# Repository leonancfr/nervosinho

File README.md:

# Projeto Macunaíma

Repositório para controle de versão de:
- Placa do Sistema Nervoso Segunda Geração, a.k.a Nervosinho
- Placa da expansão para bateria(BMS)
- Script de testes de fábrica do hardware
- Desenho da case e da caixa de transporte
- Projeto Elétrico da caixa técnica para Gabriel Cidades

## Change log das versões de hardware:
[Página do notion com o change log](https://www.notion.so/gabrieltecnologia/Change-log-das-vers-es-de-Hardware-a60b3e2a824349809387a2612b9022dc?pvs=4)

## Repositórios relacionados
- [Firmware do STM32 presente no nervosinho](https://gitlab.com/gabriel-technologia/hardware#:~:text=Firmware%20Supervisor%20Nervosinho)
- [CharlinhOS - Sistema Operacional do Processador do Nervosinho](https://gitlab.com/gabriel-technologia/iot/charlinhos)
- [CharlesGO - Software que conecta o dispositivo à infraestrutura da Gabriel](https://gitlab.com/gabriel-technologia/iot/charlesgo)

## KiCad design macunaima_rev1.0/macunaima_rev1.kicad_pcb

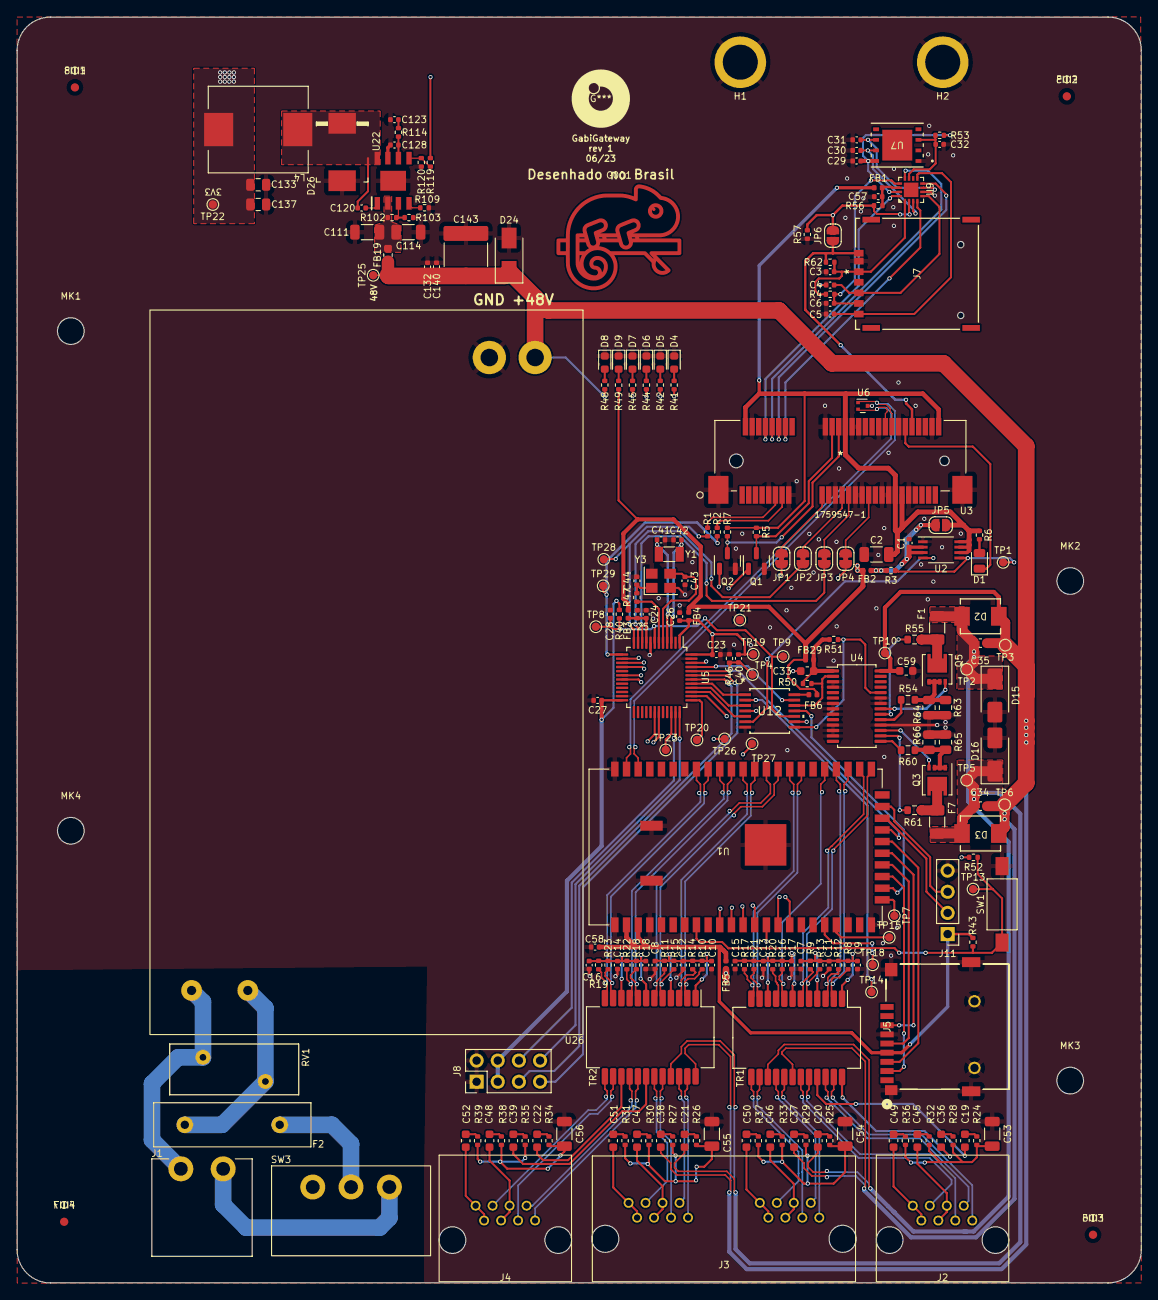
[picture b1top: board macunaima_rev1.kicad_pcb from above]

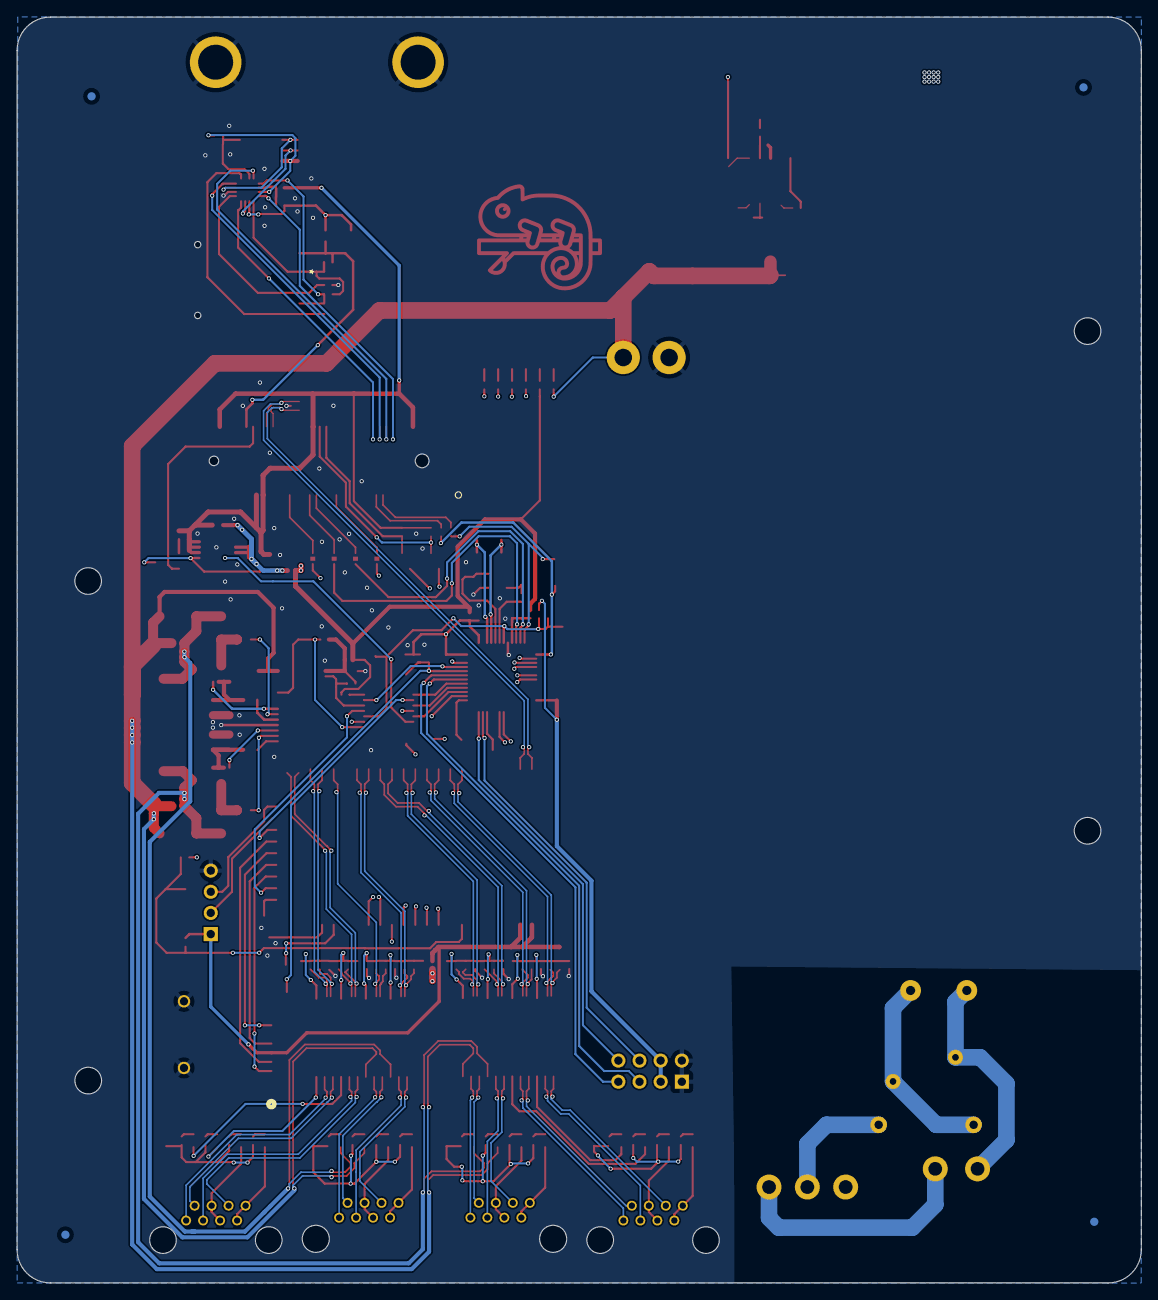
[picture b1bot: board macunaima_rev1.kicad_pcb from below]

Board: 4 copper layers, 135.0 x 152.0 mm, 239 parts (4 on the bottom side), 184 nets.

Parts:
C1: 1uF/6.3V; C_0402_1005Metric
C2: 150uF/6.3V; C_1206_3216Metric
C3, C29, C57: 100nF/6.3V; C_0402_1005Metric
C4, C5, C6, C30, C31, C32: 33pF/6.3V; C_0402_1005Metric
C7, C8, C9, C10, C11, C12, C13, C14, C15, C16, C17, C18: 0.1uF; C_0402_1005Metric
C19, C20, C21, C22, C36, C37, C38, C39, C45, C46, C47, C48, C49, C50, C51, C52: 22nF/100V; C_0603_1608Metric
C23, C26, C28, C40, C58: 100nF; C_0402_1005Metric
C24: 10nF; C_0402_1005Metric
C25: 1uF; C_0402_1005Metric
C27: 4.7uF; C_0402_1005Metric
C33: 100nF/50V; C_0603_1608Metric
C34, C35, C59: 100nF/100V; C_0603_1608Metric
C41, C42: 10pF; C_0402_1005Metric
C43, C44: 20pF; C_0402_1005Metric
C53, C54, C55, C56: 1000pF/2kV; C_1206_3216Metric
C111, C114: 2.2uF/100V; C_1206_3216Metric
C120, C132, C140: 100nF/100V; C_0402_1005Metric
C123: 6.8nF/50V; C_0402_1005Metric
C128: 39pF/50V; C_0402_1005Metric
C133, C137: 47uF/10V; C_0805_2012Metric
C143: 10uF/100V; C_2220_5650Metric
D1: LED; LED_0805_2012Metric
D2, D3: SMBJ58A; CR_SM12CA-13-F_DIO
D4, D5, D6, D7, D8, D9: LED_Small; LED_0603_1608Metric
D15, D16: 10MQ100NTRPBF; D_SMA
D24: SMAJ51A; D_SMA
D26: B560C; DO-214AB
F1, F7: 046801.5NR; Fuse_1206_3216Metric
F2: LVR100S-240; Fuse_Littelfuse-LVR100
FB1, FB2, FB3, FB4, FB5, FB6, FB29: FerriteBead_Small; L_0402_1005Metric
FB19: FerriteBead_Small; L_0603_1608Metric
FID1, FID2, FID3, FID4, FID5, FID6, FID7, FID8: Fiducial; Fiducial_1mm_Mask2mm
G001: LOGO; camaleaosilk
H1, H2: MountingHole_Pad; 4882 Standoff
J1: 127VAC/220VAC; WJ2EDGRC-5.08-2P
J2, J4: 8P8C; HC-RJ45-5JA-1-6
J3: RJ45_x2; HC-RJ45-5JA-2-6
J5: Micro_SD_Card_Det1; CONN9_0185-02_GSW
J7: XKNANO-113; XKNANO-113_XKB
J8: Conn_02x04_Odd_Even; PinHeader_2x04_P2.54mm_Vertical
J11: Conn_01x04; PinHeader_1x04_P2.54mm_Vertical
JP1, JP2, JP3, JP4: SolderJumper_2_Bridged; SolderJumper-2_P1.3mm_Bridged_RoundedPad1.0x1.5mm
JP5, JP6: SolderJumper_2_Open; SolderJumper-2_P1.3mm_Open_RoundedPad1.0x1.5mm
L4: 8.2uH; MHCC10040-8R2M-R7
MK1, MK2, MK3, MK4: Mounting_Hole; MountingHole_3.2mm_M3
Q1, Q2: PDTC143ZT; SOT-23
Q3, Q5: CSD19538Q3A; Diodes_PowerDI3333-8
R1, R2: 330R; R_0402_1005Metric
R3, R40, R43, R46, R50, R51, R52, R56, R62: 10k; R_0402_1005Metric
R4, R53: 15k; R_0402_1005Metric
R5, R7: 5k1; R_0402_1005Metric
R6: 220R; R_0402_1005Metric
R8, R9, R10, R11, R12, R13, R14, R15, R16, R17, R18, R19, R20, R21, R22, R23: 50R; R_0402_1005Metric
R24, R25, R26, R27, R28, R29, R30, R31, R32, R33, R34, R35, R36, R37, R38, R39: 75R; R_0402_1005Metric
R41, R42, R44, R45, R48, R49: R_Small; R_0402_1005Metric
R47: 390R; R_0402_1005Metric
R54, R60: 22.1R; R_0603_1608Metric
R55, R61: 47R; R_0603_1608Metric
R57: NOPOP; R_0402_1005Metric
R63, R64, R65, R66: 0.510R; R_0805_2012Metric
R102: 523k; R_0402_1005Metric
R103: 84k5; R_0402_1005Metric
R109: 162k; R_0402_1005Metric
R114: 13k; R_0402_1005Metric
R119: 36k5; R_0402_1005Metric
R120: 11k8; R_0402_1005Metric
RV1: 391KD14J; RV_Disc_D15.5mm_W6.1mm_P7.5mm
SW1: BOOT; SW_SPST_FSMSM
SW3: SW_SPDT; L102011MS02Q
TP1, TP2, TP3, TP4, TP5, TP6, TP7, TP8, TP9, TP10, TP13, TP14, TP15, TP18, TP19, TP20, TP21, TP22, TP23, TP25, TP26, TP27, TP28, TP29: TestPoint; TestPoint_Pad_D1.0mm
TR1, TR2: 30F-51NL; Transformer_Ethernet_YDS_30F-51NL_SO-24_7.1x15.1mm
U1: HLK-7628
U2: BD82006FVJ-M; BD82006FVJ-MGE2
U3: 1759547-1
U4: TPS23861; TSSOP-28_4.4x9.7mm_P0.65mm
U5: STM32F030C8Tx; LQFP-48_7x7mm_P0.5mm
U6: TPD2EUSB30; SOT-723
U7: NOPOP; SIM-ST-MFF2_HOL-M
U9: FSA2567MPX; MLP16
U12: 74HC04PW_118; TSSOP14_74HC04_NEX
U22: TPS54360BDDAR; SOIC127P600X170-9N
U26: IRM-60-48; IRM-60
Y1: 32.768kHz; Crystal_SMD_3215-2Pin_3.2x1.5mm
Y3: 8MHz; Crystal_SMD_3225-4Pin_3.2x2.5mm

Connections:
/EPHY_LED0: R41.1, U1.13 (EPHY_LED0)
/EPHY_LED1: R42.1, U1.12 (EPHY_LED1)
/EPHY_LED2: R44.1, U1.11 (EPHY_LED2)
/EPHY_LED3: R45.1, U1.10 (EPHY_LED3)
/ETH1_POE+: C34.1, C35.2, C37.1, C38.1, C59.2, C132.1, C140.1, C143.1, D2.1 (A1), D3.1 (A1), D24.1, FB19.1, R48.1, TP3.1, TP6.1, TP10.1, TP25.1, TR1.18 (CT), TR2.24 (CT), U4.28 (VPWR), U26.4 (+Vout)
/ETH1_POE-: C20.1, C35.1, D2.2 (A2), D15.1 (K), F1.2, TP2.1, TR1.15 (CT)
/ETH2_POE-: C21.1, C34.2, D3.2 (A2), D16.1 (K), F7.2, TP5.1, TR2.21 (CT)
/Ethernet connectors/TR1P1+: J2.1, TR1.23 (MX1+)
/Ethernet connectors/TR1P1-: J2.2, TR1.22 (MX1-)
/Ethernet connectors/TR1P2+: J2.3, TR1.20 (MX2+)
/Ethernet connectors/TR1P2-: J2.6, TR1.19 (MX2-)
/Ethernet connectors/TR1P3+: J3.1, TR1.17 (MX3+)
/Ethernet connectors/TR1P3-: J3.2, TR1.16 (MX3-)
/Ethernet connectors/TR1P4+: J3.3, TR1.14 (MX4+)
/Ethernet connectors/TR1P4-: J3.6, TR1.13 (MX4-)
/Ethernet connectors/TR2P1+: J3.9, TR2.23 (MX1+)
/Ethernet connectors/TR2P1-: J3.10, TR2.22 (MX1-)
/Ethernet connectors/TR2P2+: J3.11, TR2.20 (MX2+)
/Ethernet connectors/TR2P2-: J3.14, TR2.19 (MX2-)
/Ethernet connectors/TR2P3+: J4.1, TR2.17 (MX3+)
/Ethernet connectors/TR2P3-: J4.2, TR2.16 (MX3-)
/Ethernet connectors/TR2P4+: J4.3, TR2.14 (MX4+)
/Ethernet connectors/TR2P4-: J4.6, TR2.13 (MX4-)
/HLK7628_RX: TP26.1, U1.16 (UART_RXD1), U5.30 (PA9)
/HLK7628_TX: TP27.1, U1.15 (UART_TXD1), U5.31 (PA10)
/HLK-7628 Module/GPIO2: TP18.1, U1.19 (I2S_WS)
/HLK-7628 Module/GPIO3: TP15.1, U1.20 (I2S_CLK)
/HLK-7628 Module/GPIO4: TP7.1, U1.24 (I2C_SCLK)
/HLK-7628 Module/HLK7628_3V3: C58.1, FB5.2, J5.4 (VDD), J11.1, R43.2, U1.2 (3.3VD), U1.3 (3.3VD)
/HLK-7628 Module/MISO: J5.7 (DAT0), U1.28 (SPI_MISO)
/HLK-7628 Module/MOSI: J5.3 (CMD), U1.29 (SPI_MOSI)
/HLK-7628 Module/SCK: J5.5 (CLK), U1.27 (SPI_CLK)
/HLK-7628 Module/SD_CS: J5.2 (DAT3/CD), U1.26 (SPI_CS1)
/HLK-7628 Module/UART_RXD0: J11.3, U1.32 (UART_RXD0)
/HLK-7628 Module/UART_TXD0: J11.2, U1.31 (UART_TXD0)
/MDI_P0_R_N: R9.1, TR1.6 (TD2-), U1.35 (MDI_RN_P0)
/MDI_P0_R_P: R13.1, TR1.5 (TD2+), U1.34 (MDI_RP_P0)
/MDI_P0_T_N: R12.2, TR1.3 (TD1-), U1.37 (MDI_TN_P0)
/MDI_P0_T_P: R8.2, TR1.2 (TD1+), U1.36 (MDI_TP_P0)
/MDI_P1_R_N: R17.1, TR1.12 (TD4-), U1.41 (MDI_RN_P1)
/MDI_P1_R_P: R21.1, TR1.11 (TD4+), U1.40 (MDI_RP_P1)
/MDI_P1_T_N: R20.2, TR1.9 (TD3-)
/MDI_P1_T_P: R16.2, TR1.8 (TD3+), U1.38 (MDI_TP_P1)
/MDI_P2_R_N: R11.1, TR2.6 (TD2-), U1.43 (MDI_RN_P2)
/MDI_P2_R_P: R15.1, TR2.5 (TD2+), U1.42 (MDI_RP_P2)
/MDI_P2_T_N: R14.2, TR2.3 (TD1-), U1.45 (MDI_TN_P2)
/MDI_P2_T_P: R10.2, TR2.2 (TD1+), U1.44 (MDI_TP_P2)
/MDI_P3_R_N: R19.1, TR2.12 (TD4-), U1.49 (MDI_RN_P3)
/MDI_P3_R_P: R23.1, TR2.11 (TD4+), U1.48 (MDI_RP_P3)
/MDI_P3_T_N: R22.2, TR2.9 (TD3-), U1.47 (MDI_TN_P3)
/MDI_P3_T_P: R18.2, TR2.8 (TD3+), U1.46 (MDI_TP_P3)
/MODEM_CTS: JP2.1 (A), U5.11 (PA1)
/MODEM_DTR: JP4.1 (A), U5.19 (PB1)
/MODEM_EN: U2.4 (EN), U12.6 (3Y)
/MODEM_RING: JP1.1 (A), U5.18 (PB0)
/MODEM_RTS: JP3.1 (A), U5.10 (PA0)
/MODEM_RX: R1.1, TP28.1, U5.12 (PA2)
/MODEM_TX: R2.1, TP29.1, U5.13 (PA3)
/MODEM_USB_D_N: U1.55 (USB_DM), U3.36, U6.2 (D-)
/MODEM_USB_D_P: U1.54 (USB_DP), U3.38, U6.1 (D+)
/Mini PCIe/2FF_CLK: C5.1, J7.C3 (CLK), U9.9 (1CLK)
/Mini PCIe/2FF_DATA: C6.1, J7.C7 (I/O), R4.2, U9.13 (1DATA)
/Mini PCIe/2FF_RST: C4.1, J7.C2 (RST), U9.5 (1RST)
/Mini PCIe/2FF_VCC: C3.1, J7.C1 (VCC), R4.1, R62.2, U9.1 (1VSIM)
/Mini PCIe/LED_WWAN: D1.1 (K), U3.42
/Mini PCIe/MFF2_CLK: C31.1, U7.6 (CLK), U9.7 (2CLK)
/Mini PCIe/MFF2_DATA: C32.1, R53.2, U7.3 (I/O), U9.11 (2DATA)
/Mini PCIe/MFF2_RST: C30.1, U7.7 (RST), U9.3 (2RST)
/Mini PCIe/MFF2_VCC: C29.1, R53.1, U7.8 (VCC), U9.15 (2VSIM)
/Mini PCIe/MODEM_3V3: C2.1, FB1.1, JP5.2 (B), R5.1, R6.1, R7.1, U2.6 (OUT), U2.7 (OUT), U2.8 (OUT), U3.2, U3.24, U3.39, U3.41, U3.52
/Mini PCIe/MODEM_FAULT: R3.1, TP1.1, U2.5 (/OC)
/Mini PCIe/PERST: Q2.3 (C), R7.2, U3.22
/Mini PCIe/SIM_CLK: U3.12, U9.8 (CLK)
/Mini PCIe/SIM_DATA: U3.10, U9.12 (DATA)
/Mini PCIe/SIM_RST: U3.14, U9.4 (RST)
/Mini PCIe/SIM_VDD: U3.8, U9.16 (VSIM)
/Mini PCIe/SWITCH_VCC: C57.1, FB1.2, R56.2, U9.14 (VCC)
/Mini PCIe/W_DISABLE: Q1.3 (C), R5.2, U3.20
/P0RST_N: TP14.1, U1.14 (P0RST_N), U12.2 (1Y)
/PERST_CTL: Q2.1 (B), U5.15 (PA5)
/PMS_3V3: C133.2, C137.2, FB2.1, FB3.1, FB4.2, FB5.1, FB6.2, FB29.1, L4.2, R49.1, R119.1, TP22.1
/Power Management/Fase: J1.2, SW3.3 (C)
/Power Management/Neutro: J1.1, RV1.1, U26.1 (AC/N)
/Power over Ethernet/TPS23861_VDD: C33.2, FB29.2, R50.2, R51.2, U4.1 (VDD)
/RESET_POE: R50.1, U4.2 (~RESET), U12.12 (6Y)
/SHUTDOWN_POE: R51.1, U4.24 (~SHTDWN), U12.8 (4Y)
/SIMCARD_DETECT: J7.CD, JP6.1 (A), R62.1, U3.44, U5.46 (PB9)
/SIMCARD_SEL: JP6.2 (B), R56.1, R57.2, U5.14 (PA4), U9.2 (SEL)
/STM32 circuit/NRST: C28.1, R40.2, TP8.1, TP9.1, U5.7 (NRST), U12.10 (5Y)
/STM32 circuit/OSC32_IN: C42.1, U5.3 (PC14), Y1.2
/STM32 circuit/OSC32_OUT: C41.1, U5.4 (PC15), Y1.1
/STM32 circuit/OSC_IN: C43.1, U5.5 (PF0), Y3.3
/STM32 circuit/OSC_OUT: R47.1, U5.6 (PF1)
/STM32 circuit/STM32_I2C1_SCL: J8.5, U5.42 (PB6)
/STM32 circuit/STM32_I2C1_SDA: J8.7, U5.43 (PB7)
/STM32 circuit/STM32_I2C2_SCL: J8.6, U5.35 (PF6)
/STM32 circuit/STM32_I2C2_SDA: J8.8, U5.36 (PF7)
/STM32 circuit/STM32_PA15: U5.38 (PA15), U12.9 (4A)
/STM32 circuit/STM32_PB3: U5.39 (PB3), U12.5 (3A)
/STM32 circuit/STM32_PB4: U5.40 (PB4), U12.3 (2A)
/STM32 circuit/STM32_PB5: U5.41 (PB5), U12.1 (1A)
/STM32 circuit/STM32_PB8: U5.45 (PB8), U12.13 (6A)
/STM32 circuit/STM32_VDD: C23.1, C26.1, C27.1, C40.1, FB4.1, J8.3, J8.4, R40.1, TP19.1, U5.1 (VDD), U5.24 (VDD), U5.48 (VDD)
/STM32 circuit/STM32_VDDA: C24.2, C25.1, FB3.2, U5.9 (VDDA)
/STM32 circuit/SWCLK: TP20.1, U5.37 (PA14)
/STM32 circuit/SWDIO: TP23.1, U5.34 (PA13)
/STM32 circuit/~STM32_PB4: R52.2, U12.4 (2Y)
/STM32_BOOT0: C40.2, R46.1, TP4.1, U1.30 (GPIO0), U5.44 (BOOT0)
/STM32_RST: U1.25 (I2C_SD), U12.11 (5A)
/WDT_RST_N: R43.1, R52.1, SW1.1 (A), TP13.1, U1.8 (WDT_RST_N)
/W_DISABLE_CTL: Q1.1 (B), U5.16 (PA6)
GND: C1.1, C2.2, C3.2, C4.2, C5.2, C6.2, C7.2, C8.2, C9.2, C10.2, C11.1, C12.1, C13.2, C14.2, C15.2, C16.2, C17.1, C18.1, C23.2, C24.1, C25.2, C26.2, C27.2, C28.2, C29.2, C30.2, C31.2, C32.2, C33.1, C41.2, C42.2, C43.2, C44.2, C53.1, C54.1, C55.1, C56.1, C57.2, C58.2, C59.1, C111.1, C114.2, C123.1, C128.1, C132.2, C133.1, C137.1, C140.2, C143.2, D4.1 (K), D5.1 (K), D6.1 (K), D7.1 (K), D8.1 (K), D9.1 (K), D15.2 (A), D16.2 (A), D24.2, D26.A, H1.1, H2.1, J5.6 (VSS), J5.10 (SHIELD), J5.11 (SHIELD), J5.12 (SHIELD), J5.13 (SHIELD), J5.14 (SHIELD), J5.15 (SHIELD), J7.C5 (GND), J8.1, J8.2, J11.4, Q1.2 (E), Q2.2 (E), R46.2, R57.1, R63.2, R64.2, R65.1, R66.1, R103.2, R109.2, R120.2, SW1.2 (B), TP21.1, U1.1 (GND), U1.4 (GND), U1.21 (GND), U1.23 (GND), U1.56 (GND), U1.57 (GND), U1.58 (GND), U1.59 (GND), U2.1 (GND), U3.4, U3.9, U3.15, U3.18, U3.21, U3.26, U3.27, U3.28, U3.29, U3.34, U3.35, U3.37, U3.40, U3.43, U3.50, U3.53, U3.54, U4.3 (SCL), U4.4 (SDAI), U4.7 (DGND), U4.8 (SEN3), U4.9 (DRAIN3), U4.11 (KSENSB), U4.12 (SEN4), U4.13 (DRAIN4), U4.18 (KSENSA), U4.22 (AGND), U4.23 (A3), U5.8 (VSSA), U5.23 (VSS), U5.47 (VSS), U6.3 (GND), U7.1 (GND), U9.6 (GND), U12.7 (GND), U22.7 (GND), U22.9 (PAD), U26.3 (-Vout), Y3.2, Y3.4
unnamed: C8.1, C10.1, C12.2, R10.1, R11.2, R14.1, R15.2, TR2.1 (CT), TR2.4 (CT)
unnamed: C7.1, C9.1, C11.2, R8.1, R9.2, R12.1, R13.2, TR1.1 (CT), TR1.4 (CT)
unnamed: C13.1, C15.1, C17.2, R16.1, R17.2, R20.1, R21.2, TR1.7 (CT), TR1.10 (CT)
unnamed: C14.1, C16.1, C18.2, R18.1, R19.2, R22.1, R23.2, TR2.7 (CT), TR2.10 (CT)
unnamed: C19.1, TR1.21 (CT)
unnamed: C19.2, R24.1
unnamed: C20.2, R25.1
unnamed: C21.2, R26.1
unnamed: C22.1, TR2.15 (CT)
unnamed: C22.2, R34.1
unnamed: C36.1, TR1.24 (CT)
unnamed: C36.2, R28.1
unnamed: C37.2, R29.1
unnamed: C38.2, R27.1
unnamed: C39.1, TR2.18 (CT)
unnamed: C39.2, R35.1
unnamed: C44.1, R47.2, Y3.1
unnamed: C45.1, J2.4, J2.5
unnamed: C45.2, R32.1
unnamed: C46.1, J3.4, J3.5
unnamed: C46.2, R33.1
unnamed: C47.1, J3.12, J3.13
unnamed: C47.2, R30.1
unnamed: C48.1, J4.4, J4.5
unnamed: C48.2, R38.1
unnamed: C49.1, J2.7, J2.8
unnamed: C49.2, R36.1
unnamed: C50.1, J3.7, J3.8
unnamed: C50.2, R37.1
unnamed: C51.1, J3.15, J3.16
unnamed: C51.2, R31.1
unnamed: C52.1, J4.7, J4.8
unnamed: C52.2, R39.1
unnamed: C53.2, R24.2, R28.2, R32.2, R36.2
unnamed: C54.2, R25.2, R29.2, R33.2, R37.2
unnamed: C55.2, R26.2, R27.2, R30.2, R31.2
unnamed: C56.2, R34.2, R35.2, R38.2, R39.2
unnamed: C123.2, R114.2
unnamed: D1.2 (A), R6.2
unnamed: D4.2 (A), R41.2
unnamed: D5.2 (A), R42.2
unnamed: D6.2 (A), R44.2
unnamed: D7.2 (A), R45.2
unnamed: D8.2 (A), R48.2
unnamed: D9.2 (A), R49.2
unnamed: F1.1, Q5.5 (D), R55.2
unnamed: F7.1, Q3.5 (D), R61.2
unnamed: JP1.2 (B), U3.17
unnamed: JP2.2 (B), U3.23
unnamed: JP3.2 (B), U3.25
unnamed: JP4.2 (B), U3.31
unnamed: C1.2, FB2.2, JP5.1 (A), R3.2, U2.2 (IN), U2.3 (IN)
unnamed: Q3.4 (G), U4.17 (GATE1)
unnamed: Q3.1 (S), Q3.2 (S), Q3.3 (S), R60.2, R65.2, R66.2
unnamed: Q5.4 (G), U4.21 (GATE2)
unnamed: Q5.1 (S), Q5.2 (S), Q5.3 (S), R54.2, R63.1, R64.1
unnamed: R1.2, U3.11
unnamed: R2.2, U3.13
unnamed: F2.1, SW3.2 (B)
unnamed: R61.1, U4.16 (DRAIN1)
unnamed: R55.1, U4.20 (DRAIN2)
unnamed: R60.1, U4.15 (SEN1)
unnamed: R54.1, U4.19 (SEN2)
unnamed: FB6.1, U12.14 (VCC)
unnamed: C120.1, U22.1 (BOOT)
unnamed: C128.2, R114.1, U22.6 (COMP)
unnamed: R102.2, R103.1, U22.3 (EN)
unnamed: R119.2, R120.1, U22.5 (FB)
unnamed: R109.1, U22.4 (RT/CLK)
unnamed: C120.2, D26.K, L4.1, U22.8 (SW)
unnamed: C111.2, C114.1, FB19.2, R102.1, U22.2 (VIN)
unnamed: F2.2, RV1.2, U26.2 (AC/L)

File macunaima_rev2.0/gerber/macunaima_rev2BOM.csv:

Id,Designator,Footprint,Quantity,Comment,LCSC Part Number
11,C1,C_0402_1005Metric,1,1uF/6.3V,C307427
18,"C111,C114",C_1206_3216Metric,2,2.2uF/100V,C170101
9,"C120,C140,C132",C_0402_1005Metric,3,100nF/100V,C162178
57,C123,C_0402_1005Metric,1,6.8nF/50V,C2760541
48,C128,C_0402_1005Metric,1,39pF/50V,C1563
62,"C137,C133",C_0805_2012Metric,2,47uF/10V,C76636
88,C143,C_2220_5650Metric,1,10uF/100V,C153035
75,C2,C_1206_3216Metric,1,150uF/6.3V,C528968
22,"C23,C60,C28,C26,C58,C40",C_0402_1005Metric,6,100nF,C162178
61,C24,C_0402_1005Metric,1,10nF,C527014
6,C25,C_0402_1005Metric,1,1uF,C14445
40,C27,C_0402_1005Metric,1,4.7uF,C368809
80,"C3,C57,C29",C_0402_1005Metric,3,100nF/6.3V,C1525
4,"C32,C5,C30,C4,C6,C31",C_0402_1005Metric,6,33pF/6.3V,C1562
79,C33,C_0603_1608Metric,1,100nF/50V,C42998
41,"C34,C35,C59",C_0603_1608Metric,3,100nF/100V,C15725
2,"C38,C36,C46,C49,C45,C52,C48,C50,C37,C51,C21,C47,C19,C39,C20,C22",C_0603_1608Metric,16,22nF/100V,C313105
8,"C41,C42",C_0402_1005Metric,2,10pF,C513681
44,"C43,C44",C_0402_1005Metric,2,20pF,C1554
50,"C53,C54,C56,C55",C_1206_3216Metric,4,1000pF/2kV,C9196
19,"C9,C11,C18,C15,C12,C16,C17,C10,C7,C14,C8,C13",C_0402_1005Metric,12,0.1uF,C162178
15,D1,LED_0805_2012Metric,1,LED,C434432
59,"D16,D15",D_SMA,2,10MQ100NTRPBF,C241877
28,D24,D_SMA,1,SMAJ51A,C309894
54,D26,DO-214AB,1,B560C,C85100
34,"D3,D2",CR_SM12CA-13-F_DIO,2,SMBJ58A,C707476
47,"D7,D8,D4,D5,D6,D9",LED_0805_2012Metric,6,LED_Small,C434432
52,"F1,F7",Fuse_1206_3216Metric,2,046801.5NR,C151143
17,F2,Fuse_Littelfuse-LVR100,1,LVR100S-240,C20876
31,FB19,L_0603_1608Metric,1,FerriteBead_Small,C394410
27,"FB6,FB29,FB2,FB1,FB4,FB5,FB3",L_0402_1005Metric,7,FerriteBead_Small,C275476
35,"FID3,FID1,FID2,FID4,FID6,FID8,FID7,FID5",Fiducial_1mm_Mask2mm,8,Fiducial,NOPOP
82,"H1,H2",SMTSO2545CTJ,2,MountingHole_Pad,C2916325
66,J1,WJ2EDGRC-5.08-2P,1,127VAC/220VAC,C3697
33,J11,PinHeader_1x04_P2.54mm_Vertical,1,Conn_01x04,NOPOP
36,J2,HC-RJ45-5JA-1-6,1,8P8C,C3000176
72,J3,HC-RJ45-5JA-2-4,1,RJ45_x2,C3000179
97,J4,HC-RJ45-5JA-1-6-L,1,8P8C,C3000188
51,J5,CONN9_0185-02_GSW,1,Micro_SD_Card_Det1,C5155564
56,J6,KF235-5.0-2P,1,Conn_01x02,C475172
77,J7,XKNANO-113_XKB,1,XKNANO-113,C381071
10,J8,PinHeader_2x04_P2.54mm_Vertical,1,Conn_02x04_Odd_Even,NOPOP
58,J9,KH-IPEX-SMAKWE-B120H,1,Conn_01x01,C530651
12,"JP1,JP3,JP4,JP2",SolderJumper-2_P1.3mm_Bridged_RoundedPad1.0x1.5mm,4,SolderJumper_2_Bridged,NOPOP
63,"JP6,JP5,JP8,JP9,JP7",SolderJumper-2_P1.3mm_Open_RoundedPad1.0x1.5mm,5,SolderJumper_2_Open,NOPOP
68,L4,MHCC10040-8R2M-R7,1,8.2uH,C285788
30,"MK2,MK1,MK3,MK4",MountingHole_4.3mm_M4,4,Mounting_Hole,NOPOP
70,"Q2,Q1",SOT-23,2,PDTC143ZT,C426852
46,"Q5,Q3",Diodes_PowerDI3333-8,2,CSD19538Q3A,C478471
49,"R1,R2",R_0402_1005Metric,2,330R,C105875
81,R102,R_0402_1005Metric,1,523k,C27011
94,R103,R_0402_1005Metric,1,84k5,C185390
67,R109,R_0402_1005Metric,1,162k,C321325
85,R114,R_0402_1005Metric,1,13k,C25754
74,R119,R_0402_1005Metric,1,36k5,C15011
96,R120,R_0402_1005Metric,1,11k8,C189472
21,"R21,R19,R16,R15,R12,R8,R18,R9,R20,R23,R17,R11,R14,R10,R22,R13",R_0402_1005Metric,16,50R,C279983
5,"R31,R27,R30,R35,R32,R24,R39,R38,R29,R34,R37,R25,R33,R26,R28,R36",R_0402_1005Metric,16,75R,C114757
20,"R4,R53",R_0402_1005Metric,2,15k,C25756
32,"R45,R49,R42,R41,R44",R_0402_1005Metric,5,300R,C25159
78,R47,R_0402_1005Metric,1,390R,C137997
69,"R5,R7",R_0402_1005Metric,2,5k1,C25905
39,"R55,R61",R_0603_1608Metric,2,47R/5%/0.1W,C209152
87,R57,R_0402_1005Metric,1,NOPOP,NOPOP
71,R6,R_0402_1005Metric,1,220R,C112291
65,"R60,R54",R_0603_1608Metric,2,22.1R/1%/0.1W,C22958
42,"R64,R66,R65,R63",R_0805_2012Metric,4,0.510R/1%/0.25W,C859812
38,"R67,R68,R58,R59",R_0402_1005Metric,4,4k7,C25900
7,"R74,R51,R43,R46,R73,R40,R56,R69,R62,R52,R50,R48,R71,R3",R_0402_1005Metric,14,10k,C25744
84,RV1,RV_Disc_D15.5mm_W6.1mm_P7.5mm,1,391KD14J,C3019445
83,SW1,SW_SPST_FSMSM,1,BOOT,C492866
76,SW3,SS-12D06L5,1,SW_SPDT,C319015
13,"TP12,TP11",TestPoint_Pad_D1.0mm,2,MFF2_VCC,NOPOP
93,TP13,TestPoint_Pad_D1.0mm,1,WDRST,NOPOP
95,TP2,TestPoint_Pad_D1.0mm,1,POE1-,NOPOP
24,"TP20,3V3,TP25,TP26,TP23,TP15,TP28,TP27,TP10,TP21,TP18,TP29,TP6,TP14,TP1,TP4",TestPoint_Pad_D1.0mm,16,TestPoint,NOPOP
53,TP22,TestPoint_Pad_D1.0mm,1,3V3,NOPOP
16,TP3,TestPoint_Pad_D1.0mm,1,POE1+,NOPOP
64,TP5,TestPoint_Pad_D1.0mm,1,POE2-,NOPOP
86,"TP7,TP7",TestPoint_Pad_D1.0mm,2,BOOT,NOPOP
45,TP8,TestPoint_Pad_D1.0mm,1,2FF_VCC,NOPOP
89,TP9,TestPoint_Pad_D1.0mm,1,STMRST,NOPOP
26,"TR1,TR2",Transformer_Ethernet_YDS_30F-51NL_SO-24_7.1x15.1mm,2,30F-51NL,C123168
90,U1,HLK-7628,1,HLK-7628,C209920
1,U12,TSSOP14_74HC04_NEX,1,74HC04PW_118,C80000
60,U2,BD82006FVJ-MGE2,1,BD82006FVJ-M,C2150448
92,U22,SOIC127P600X170-9N,1,TPS54360BDDAR,C524806
25,U26,IRM-60,1,IRM-60-48,NOPOP
43,U3,1759547-1,1,1759547-1,C428485
14,U4,TSSOP-28_4.4x9.7mm_P0.65mm,1,TPS23861,C93245
55,U5,LQFP-48_7x7mm_P0.5mm,1,STM32F030C8Tx,C40053
23,U6,SOT-723,1,TPD2EUSB30,C2997271
91,U7,SIM-ST-MFF2_HOL-M,1,NOPOP,NOPOP
37,U8,SOIC127P600X175-8N,1,M24C16-RMN6TP,C79946
29,U9,MLP16,1,FSA2567MPX,C512961
3,Y1,Crystal_SMD_3215-2Pin_3.2x1.5mm,1,32.768kHz,C32346
73,Y3,Crystal_SMD_3225-4Pin_3.2x2.5mm,1,8MHz,C2682775

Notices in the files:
parts and their libraries:
Copyright 2021 Accelerated Designs. All rights reserved.
